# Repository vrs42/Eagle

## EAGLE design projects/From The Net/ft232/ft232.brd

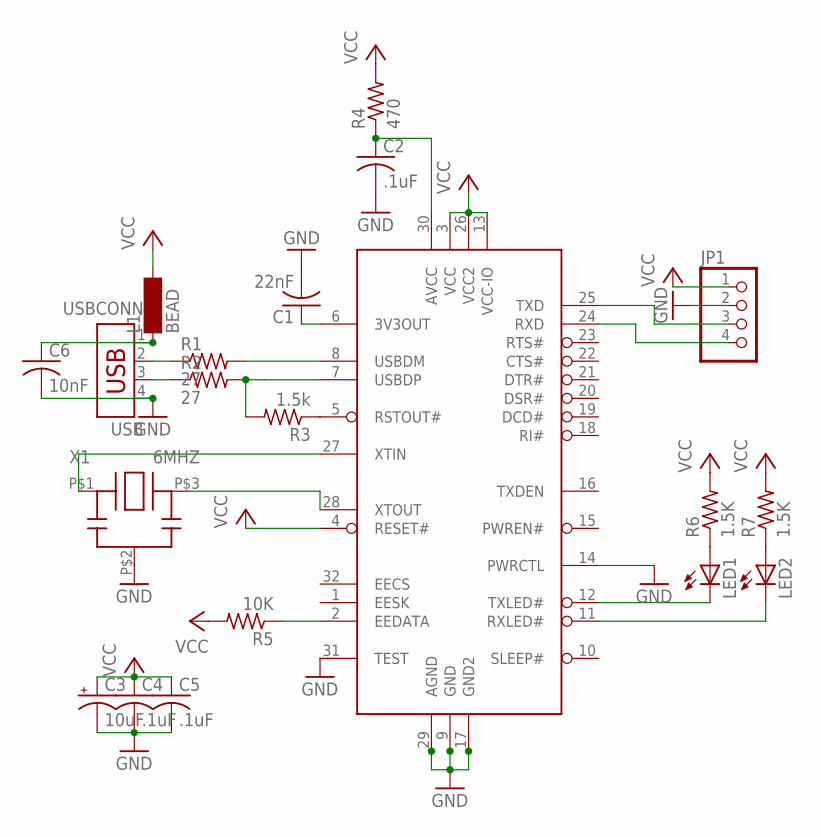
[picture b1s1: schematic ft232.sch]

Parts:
C1: 22nF; C1206
C2, C4, C5: .1uF; C1206
C3: 10uF; B/3528-21R
C6: 10nF; C1206
IC1: FT232; SQFP-S-7X7-32
JP1: PINHD-1X4; 1X04
L1: BEAD; SM-1206
LED1, LED2: LEDSMT1206; 1206
R1, R2: 27; R1206
R3: 1.5k; R1206
R4: 470; R1206
R5: 10K; R1206
R6, R7: 1.5K; R1206
USBCONN: USB
X1: 6MHZ; ZTT_XTAL

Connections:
GND: C1.2, C2.2, C3.-, C4.2, C5.2, C6.2, IC1.9 (GND), IC1.14 (PWRCTL), IC1.17 (GND2), IC1.29 (AGND), IC1.31 (TEST), JP1.2, USBCONN.4, X1.P$2 (GND)
unnamed: R1.1, USBCONN.2
unnamed: R2.1, USBCONN.3
unnamed: IC1.7 (USBDP), R2.2, R3.2
unnamed: IC1.8 (USBDM), R1.2
unnamed: IC1.5 (RSTOUT#), R3.1
unnamed: C2.1, IC1.30 (AVCC), R4.1
unnamed: C1.1, IC1.6 (3V3OUT)
unnamed: IC1.2 (EEDATA), R5.1
unnamed: IC1.28 (XTOUT), X1.P$3 (OUT)
unnamed: IC1.27 (XTIN), X1.P$1 (IN)
unnamed: IC1.25 (TXD), JP1.3
unnamed: IC1.24 (RXD), JP1.4
unnamed: IC1.11 (RXLED#), LED2.C
unnamed: IC1.12 (TXLED#), LED1.C
unnamed: LED1.A, R6.1
unnamed: LED2.A, R7.1
unnamed: C6.1, L1.1, USBCONN.1
VCC: C3.+, C4.1, C5.1, IC1.3 (VCC), IC1.4 (RESET#), IC1.13 (VCC-IO), IC1.26 (VCC2), JP1.1, L1.2, R4.2, R5.2, R6.2, R7.2

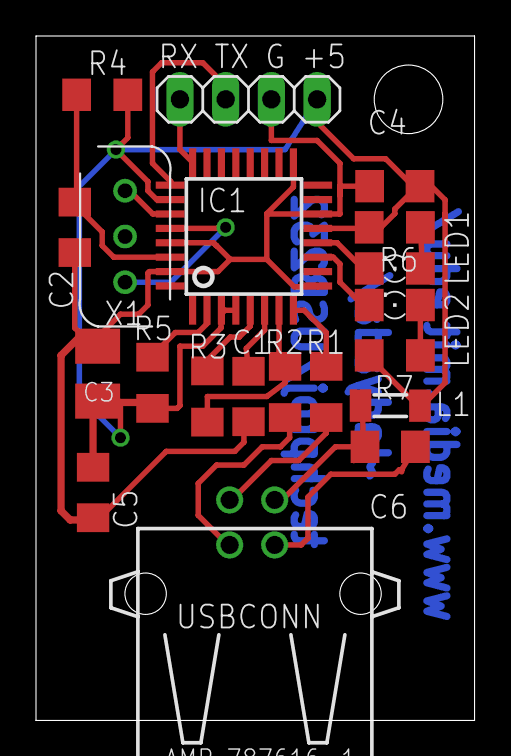
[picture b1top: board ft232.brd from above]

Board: 2 copper layers, 24.4 x 38.0 mm, 20 parts (0 on the bottom side), 19 nets.

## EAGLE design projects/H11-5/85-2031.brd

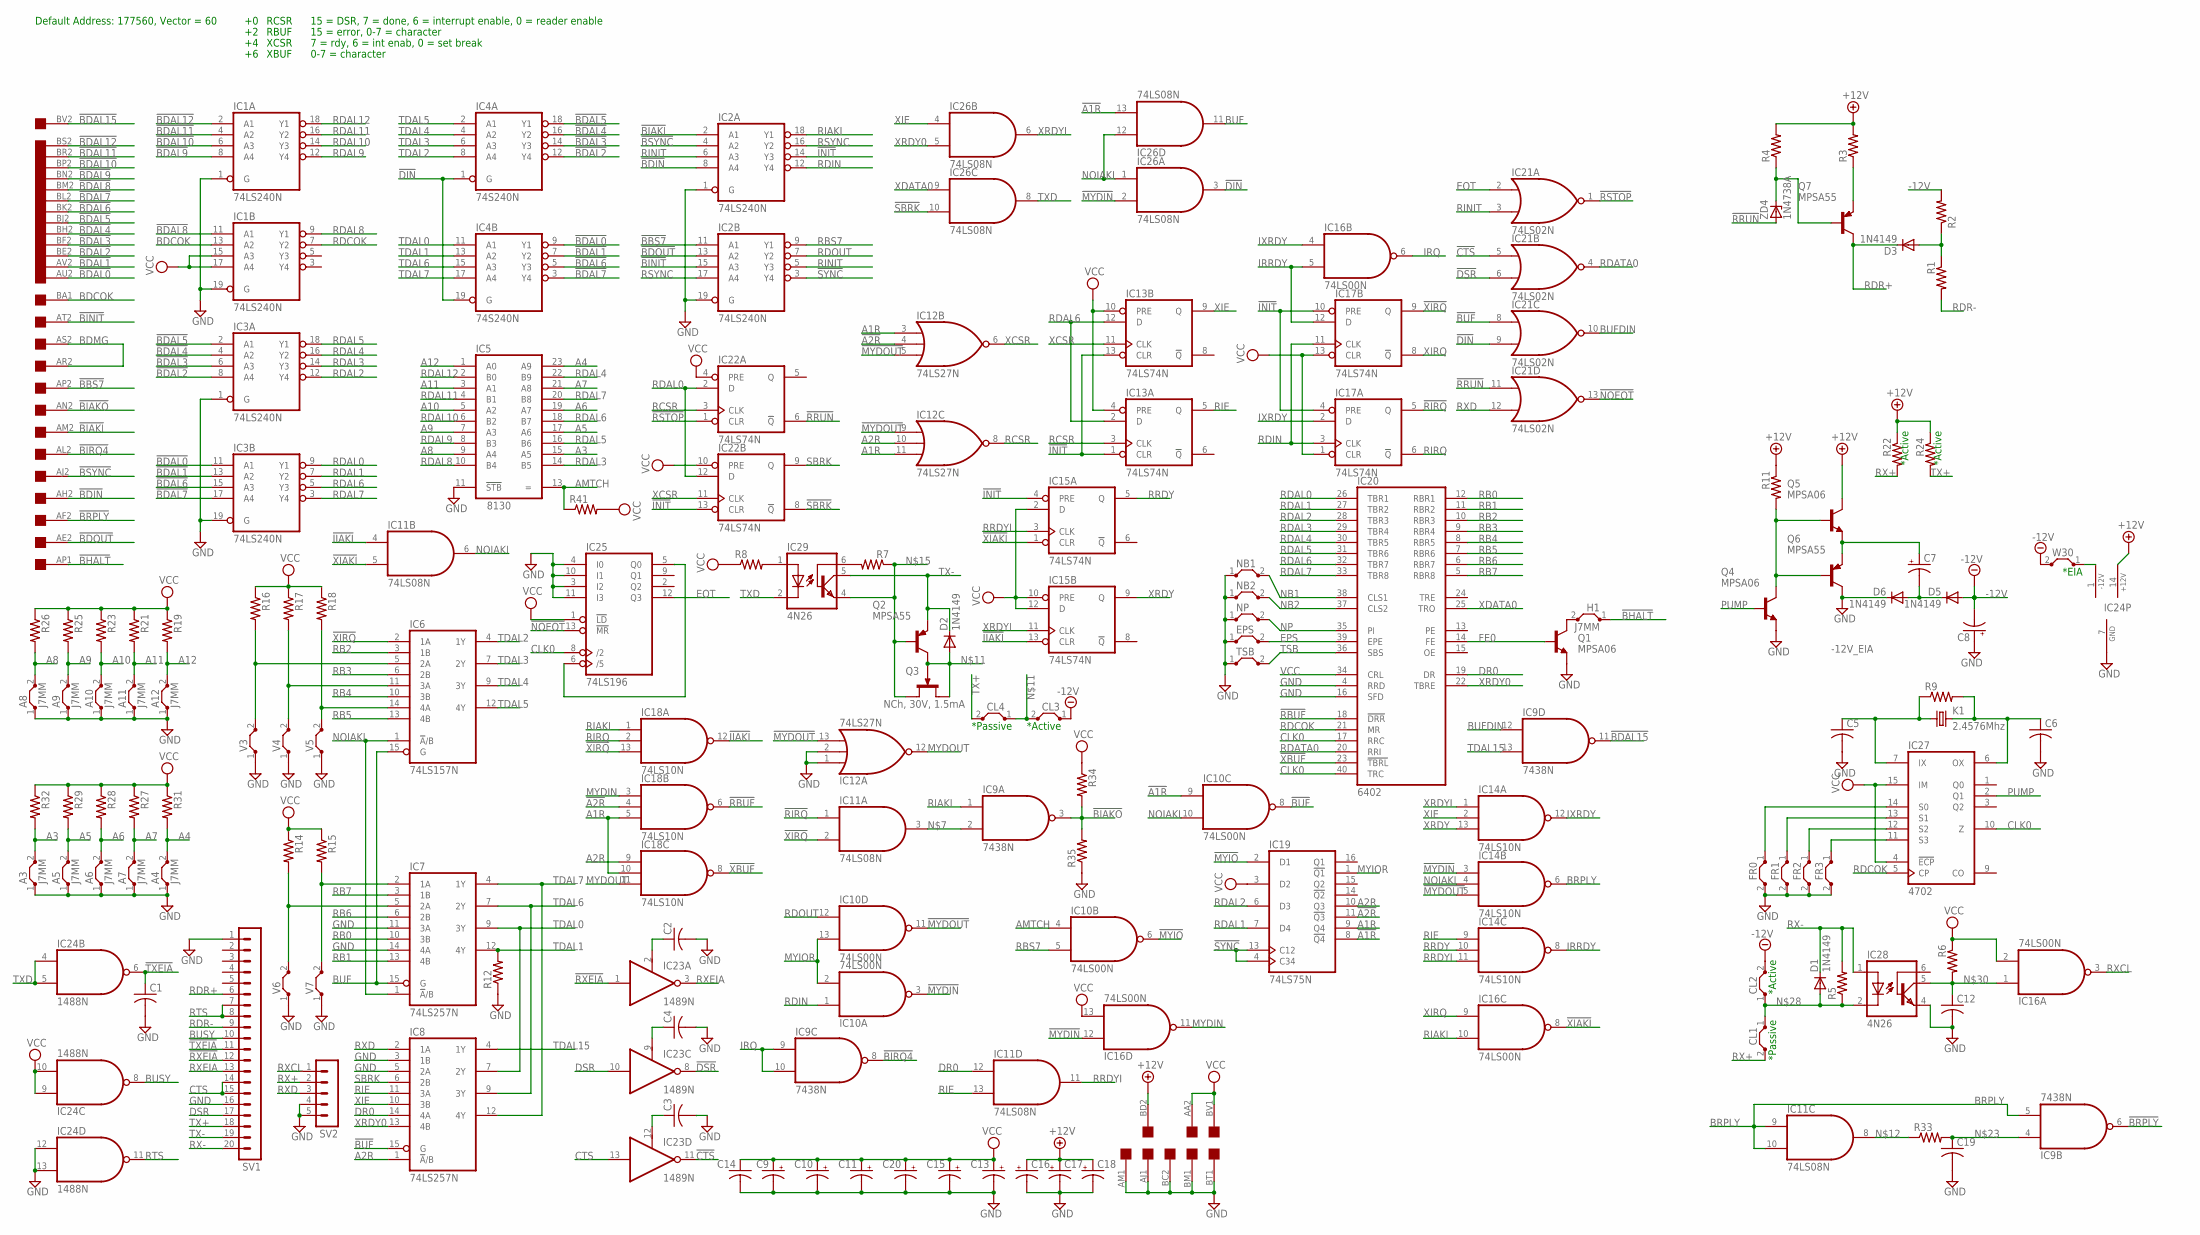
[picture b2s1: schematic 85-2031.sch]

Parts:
A3, A4, A5, A6, A7, A8, A9, A10, A11, A12: J7MM; 07
C1, C2, C3, C4, C5, C6, C12, C14, C19: C-US075-032X103; C075-032X103
C7, C8, C9, C10, C11, C13, C15, C16, C17, C18, C20: CPOL-USB45181B; B45181B
CL1, CL2, CL3, CL4: J7MM; 07
D1, D2, D3, D5, D6: 1N4149; DO35-10
EDGE$: DOUBLE; EDGE-CON4
EPS: J7MM; 07
FR0, FR1, FR2, FR3: J7MM; 07
H1: J7MM; 07
IC1, IC2, IC3: 74LS240N; DIL20
IC4: 74S240N; DIL20
IC5: 8130; DIL24
IC6: 74LS157N; DIL16
IC7, IC8: 74LS257N; DIL16
IC9: 7438N; DIL14
IC10, IC16: 74LS00N; DIL14
IC11, IC26: 74LS08N; DIL14
IC12: 74LS27N; DIL14
IC13, IC15, IC17, IC22: 74LS74N; DIL14
IC14, IC18: 74LS10N; DIL14
IC19: 74LS75N; DIL16
IC20: 6402; DIL40
IC21: 74LS02N; DIL14
IC23: 1489N; DIL14
IC24: 1488N; DIL14
IC25: 74LS196; DIL14
IC27: 4702; DIL16
IC28, IC29: 4N26; DIL06
K1: 2.4576Mhz; HC33U-H
NB1, NB2: J7MM; 07
NP: J7MM; 07
Q1, Q4, Q5: MPSA06; TO92L
Q2, Q6, Q7: MPSA55; TO92L
Q3: NCh, 30V, 1.5mA; TO18E
R1, R2, R3, R4, R5, R6, R7, R8, R9, R12, R14, R15, R16, R17, R18, R19, R21, R22, R23, R24, R25, R26, R27, R28, R29, R31, R32, R33, R34, R35, R41: R-US_0207/10; 0207/10
R11: R-US_0411/12; 0411/12
SV1: MA20-1
SV2: MA05-1
TSB: J7MM; 07
V3, V4, V5, V6, V7: J7MM; 07
W30: J7MM; 07
ZD4: 1N4738A; DO41Z10

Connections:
!A1R: IC10.9 (I0), IC19.8 (!Q4), IC26.13 (I1)
!A2R: IC12.4 (I1), IC18.4 (I1), IC19.11 (!Q3)
!BBS7: EDGE$.AP2, IC2.11 (A1)
!BDAL0: EDGE$.AU2, IC3.11 (A1), IC4.9 (Y1)
!BDAL1: EDGE$.AV2, IC3.13 (A2), IC4.7 (Y2)
!BDAL2: EDGE$.BE2, IC3.8 (A4), IC4.12 (Y4)
!BDAL3: EDGE$.BF2, IC3.6 (A3), IC4.14 (Y3)
!BDAL4: EDGE$.BH2, IC3.4 (A2), IC4.16 (Y2)
!BDAL5: EDGE$.BJ2, IC3.2 (A1), IC4.18 (Y1)
!BDAL6: EDGE$.BK2, IC3.15 (A3), IC4.5 (Y3)
!BDAL7: EDGE$.BL2, IC3.17 (A4), IC4.3 (Y4)
!BDAL8: EDGE$.BM2, IC1.11 (A1)
!BDAL9: EDGE$.BN2, IC1.8 (A4)
!BDAL10: EDGE$.BP2, IC1.6 (A3)
!BDAL11: EDGE$.BR2, IC1.4 (A2)
!BDAL12: EDGE$.BS2, IC1.2 (A1)
!BDAL15: EDGE$.BV2, IC9.11 (O)
!BDIN: EDGE$.AH2, IC2.8 (A4)
!BDOUT: EDGE$.AE2, IC2.13 (A2)
!BHALT: EDGE$.AP1, H1.1
!BIAKI: EDGE$.AM2, IC2.2 (A1)
!BIAKO: EDGE$.AN2, IC9.3 (O), R34.2, R35.2
!BINIT: EDGE$.AT2, IC2.15 (A3)
!BIRQ4: EDGE$.AL2, IC9.8 (O)
!BRPLY: EDGE$.AF2, IC9.6 (O)
!BSYNC: EDGE$.AJ2, IC2.4 (A2)
!BUF: IC8.15 (G), IC10.8 (O), IC21.8 (I0)
!CTS: IC21.5 (I0), IC23.11 (O)
!DIN: IC4.1 (G), IC4.19 (G), IC21.9 (I1), IC26.3 (O)
!DSR: IC21.6 (I1), IC23.8 (O)
!IIAKI: IC11.4 (I0), IC15.13 (CLR), IC18.12 (O)
!INIT: IC2.14 (Y3), IC13.1 (CLR), IC13.13 (CLR), IC15.4 (PRE), IC17.4 (PRE), IC17.10 (PRE), IC22.13 (CLR)
!MYDIN: IC10.3 (O), IC14.3 (I0), IC16.12 (I0), IC26.2 (I1)
!MYDOUT: IC10.11 (O), IC12.5 (I2), IC12.9 (I0), IC12.13 (I2), IC14.5 (I2)
!MYIO: IC10.6 (O), IC19.2 (D1)
!NOEOT: IC21.13 (O), IC25.13 (!MR)
!RBUF: IC18.6 (O), IC20.18 (!DRR)
!RIRQ: IC11.1 (I0), IC17.5 (Q)
!RRUN: IC21.11 (I0), IC22.6 (!Q), ZD4.A
!RSTOP: IC21.1 (O), IC22.1 (CLR)
!RXEIA: IC23.1 (I), SV1.12
!SBRK: IC22.8 (!Q), IC26.10 (I1)
!SYNC: IC2.3 (Y4), IC19.4 (C34), IC19.13 (C12)
!TXEIA: C1.1, IC24.6 (O), SV1.11
!XBUF: IC18.8 (O), IC20.23 (!TBRL)
!XIAKI: IC11.5 (I1), IC15.1 (CLR), IC16.8 (O)
!XIRQ: IC6.2 (1A), IC11.2 (I1), IC17.9 (Q), IC18.13 (I2)
+12V: C16.+, C17.+, C18.+, EDGE$.BD2, IC24.14 (+12V), Q5.3 (C), R3.2, R4.2, R11.1, R22.1, R24.1
-12V: C8.-, CL2.2, CL3.1, D5.A, R2.2, W30.2
-12V_EIA: IC24.1 (-12V), W30.1
A1R: IC12.3 (I0), IC12.11 (I2), IC18.5 (I2), IC18.10 (I1), IC19.9 (Q4)
A2R: IC8.1 (!A!/B), IC12.10 (I1), IC18.9 (I0), IC19.10 (Q3)
A3: A3.2, IC5.15 (A5), R32.2
A4: A4.2, IC5.23 (A9), R31.2
A5: A5.2, IC5.17 (A6), R29.2
A6: A6.2, IC5.19 (A7), R28.2
A7: A7.2, IC5.21 (A8), R27.2
A8: A8.2, IC5.9 (A4), R26.2
A9: A9.2, IC5.7 (A3), R25.2
A10: A10.2, IC5.5 (A2), R23.2
A11: A11.2, IC5.3 (A1), R21.2
A12: A12.2, IC5.1 (A0), R19.2
AMTCH: IC5.13 (=), IC10.4 (I0), R41.1
BDCOK: EDGE$.BA1, IC1.13 (A2)
BDMG: EDGE$.AR2, EDGE$.AS2
BRPLY: IC9.5 (I1), IC11.9 (I0), IC11.10 (I1), IC14.6 (O)
BUF: IC6.15 (G), IC7.15 (G), IC26.11 (O)
BUFDIN: IC9.12 (I0), IC21.10 (O)
BUSY: IC24.8 (O), SV1.10
CLK0: IC20.17 (RRC), IC20.40 (TRC), IC25.8 (/2), IC27.10 (Z)
CTS: IC23.13 (I), SV1.14, SV1.15
DR0: IC8.14 (4A), IC11.12 (I0), IC20.19 (DR)
DSR: IC23.10 (I), SV1.17
EOT: IC21.2 (I0), IC25.12 (Q3)
EPS: EPS.2, IC20.39 (EPE)
FE0: IC20.14 (FE), Q1.2 (B)
GND: A3.1, A4.1, A5.1, A6.1, A7.1, A8.1, A9.1, A10.1, A11.1, A12.1, C1.2, C2.2, C3.2, C4.2, C5.2, C6.2, C8.+, C9.-, C10.-, C11.-, C12.2, C13.-, C14.2, C15.-, C16.-, C17.-, C18.-, C19.2, C20.-, D6.C, EDGE$.AJ1, EDGE$.AM1, EDGE$.BC2, EDGE$.BM1, EDGE$.BT1, EPS.1, FR0.2, FR1.2, FR2.2, FR3.2, IC1.1 (G), IC1.10 (GND), IC1.19 (G), IC2.1 (G), IC2.10 (GND), IC2.19 (G), IC3.1 (G), IC3.10 (GND), IC3.19 (G), IC4.10 (GND), IC5.11 (!STB), IC5.12 (GND), IC6.8 (GND), IC7.8 (GND), IC7.11 (3A), IC7.14 (4A), IC8.3 (1B), IC8.5 (2A), IC8.8 (GND), IC9.7 (GND), IC10.7 (GND), IC11.7 (GND), IC12.1 (I0), IC12.2 (I1), IC12.7 (GND), IC13.7 (GND), IC14.7 (GND), IC15.7 (GND), IC16.7 (GND), IC17.7 (GND), IC18.7 (GND), IC19.12 (GND), IC20.3 (GND), IC20.4 (RRD), IC20.16 (SFD), IC21.7 (GND), IC22.7 (GND), IC23.7 (GND), IC24.7 (GND), IC24.12 (I0), IC24.13 (I1), IC25.3 (I2), IC25.4 (I0), IC25.7 (GND), IC25.10 (I1), IC25.11 (I3), IC26.7 (GND), IC27.8 (GND), IC28.4 (EMI), NB1.1, NB2.1, NP.1, Q1.1 (E), Q4.1 (E), Q6.3 (C), R12.1, R35.1, SV1.1, SV1.16, SV2.4, SV2.5, TSB.1, V3.1, V4.1, V5.1, V6.1, V7.1
IRQ: IC9.9 (I0), IC9.10 (I1), IC16.6 (O)
IRRDY: IC14.8 (O), IC16.5 (I1), IC17.12 (D)
IXRDY: IC14.12 (O), IC16.4 (I0), IC17.2 (D)
MYDIN: IC16.11 (O), IC18.3 (I0)
MYDOUT: IC12.12 (O), IC18.11 (I2)
MYIOR: IC10.2 (I1), IC10.13 (I1), IC19.1 (!Q1)
unnamed: C2.1, IC23.2 (RC)
unnamed: FR0.1, IC27.14 (S0)
unnamed: H1.2, Q1.3 (C)
unnamed: FR1.1, IC27.13 (S1)
unnamed: FR2.1, IC27.12 (S2)
unnamed: FR3.1, IC27.11 (S3)
unnamed: IC9.2 (I1), IC11.3 (O)
unnamed: IC6.14 (4A), R18.2, V5.2
unnamed: C5.1, IC27.7 (IX), K1.1, R9.1
unnamed: C6.1, IC27.6 (OX), K1.2, R9.2
unnamed: CL3.2, CL4.1, D2.A, Q2.3 (C), Q3.D, Q3.G
unnamed: IC11.8 (O), R33.1
unnamed: IC29.6 (BAS), R7.2
unnamed: IC29.4 (EMI), Q2.2 (B), Q3.S, R7.1
unnamed: IC29.1 (A), R8.2
unnamed: IC7.2 (1A), R15.2, V7.2
unnamed: IC7.5 (2A), R14.2, V6.2
unnamed: C4.1, IC23.9 (RC)
unnamed: C7.-, D5.C, D6.A
unnamed: IC6.11 (3A), R17.2, V4.2
unnamed: C7.+, Q5.1 (E), Q6.1 (E)
unnamed: C19.1, IC9.4 (I0), R33.2
unnamed: IC6.5 (2A), R16.2, V3.2
unnamed: C3.1, IC23.12 (RC)
unnamed: Q4.3 (C), Q5.2 (B), Q6.2 (B), R11.2
unnamed: D3.A, R1.1, R2.1
unnamed: CL1.1, CL2.1, D1.A, IC28.2 (C), R5.1
unnamed: Q7.2 (B), R4.1, ZD4.C
unnamed: C12.1, IC16.1 (I0), IC28.5 (COL), R6.2
unnamed: Q7.1 (E), R3.1
unnamed: IC25.5 (Q0), IC25.6 (/5)
NB1: IC20.38 (CLS1), NB1.2
NB2: IC20.37 (CLS2), NB2.2
NOIAKI: IC6.1 (!A!/B), IC7.1 (!A!/B), IC10.10 (I1), IC11.6 (O), IC14.4 (I1), IC26.1 (I0), IC26.12 (I0)
NP: IC20.35 (PI), NP.2
PUMP: IC27.2 (Q1), Q4.2 (B)
RB0: IC7.10 (3B), IC20.12 (RBR1)
RB1: IC7.13 (4B), IC20.11 (RBR2)
RB2: IC6.3 (1B), IC20.10 (RBR3)
RB3: IC6.6 (2B), IC20.9 (RBR4)
RB4: IC6.10 (3B), IC20.8 (RBR5)
RB5: IC6.13 (4B), IC20.7 (RBR6)
RB6: IC7.6 (2B), IC20.6 (RBR7)
RB7: IC7.3 (1B), IC20.5 (RBR8)
RBS7: IC2.9 (Y1), IC10.5 (I1)
RCSR: IC12.8 (O), IC13.3 (CLK), IC22.3 (CLK)
RDAL0: IC3.9 (Y1), IC20.26 (TBR1), IC22.2 (D), IC22.12 (D)
RDAL1: IC3.7 (Y2), IC19.7 (D4), IC20.27 (TBR2)
RDAL2: IC3.12 (Y4), IC19.6 (D3), IC20.28 (TBR3)
RDAL3: IC3.14 (Y3), IC5.14 (B5), IC20.29 (TBR4)
RDAL4: IC3.16 (Y2), IC5.22 (B9), IC20.30 (TBR5)
RDAL5: IC3.18 (Y1), IC5.16 (B6), IC20.31 (TBR6)
RDAL6: IC3.5 (Y3), IC5.18 (B7), IC13.2 (D), IC13.12 (D), IC20.32 (TBR7)
RDAL7: IC3.3 (Y4), IC5.20 (B8), IC20.33 (TBR8)
RDAL8: IC1.9 (Y1), IC5.10 (B4)
RDAL9: IC1.12 (Y4), IC5.8 (B3)
RDAL10: IC1.14 (Y3), IC5.6 (B2)
RDAL11: IC1.16 (Y2), IC5.4 (B1)
RDAL12: IC1.18 (Y1), IC5.2 (B0)
RDATA0: IC20.20 (RRI), IC21.4 (O)
RDCOK: IC1.7 (Y2), IC20.21 (MR), IC27.5 (CP)
RDIN: IC2.12 (Y4), IC10.1 (I0), IC17.3 (CLK), IC17.11 (CLK)
RDOUT: IC2.7 (Y2), IC10.12 (I0)
RDR+: D3.C, Q7.3 (C), SV1.6
RDR-: R1.2, SV1.9
RIAKI: IC2.18 (Y1), IC9.1 (I0), IC16.10 (I1), IC18.1 (I0)
RIE: IC8.11 (3A), IC11.13 (I1), IC13.5 (Q), IC14.9 (I0)
RINIT: IC2.5 (Y3), IC2.6 (A3), IC21.3 (I1)
RIRQ: IC17.6 (!Q), IC18.2 (I1)
RRDY: IC14.10 (I1), IC15.5 (Q)
RRDYI: IC11.11 (O), IC14.11 (I2), IC15.3 (CLK)
RSYNC: IC2.16 (Y2), IC2.17 (A4)
RTS: IC24.11 (O), SV1.7, SV1.8
RX+: CL1.2, R22.2, SV2.2
RX-: D1.C, IC28.1 (A), R5.2, SV1.20
RXCL: IC16.3 (O), SV2.1
RXD: IC8.2 (1A), IC21.12 (I1), SV2.3
RXEIA: IC23.3 (O), SV1.13
SBRK: IC8.6 (2B), IC22.9 (Q)
TDAL0: IC4.11 (A1), IC7.9 (3Y), IC8.7 (2Y)
TDAL1: IC4.13 (A2), IC7.12 (4Y), R12.2
TDAL2: IC4.8 (A4), IC6.4 (1Y)
TDAL3: IC4.6 (A3), IC6.7 (2Y)
TDAL4: IC4.4 (A2), IC6.9 (3Y)
TDAL5: IC4.2 (A1), IC6.12 (4Y)
TDAL6: IC4.15 (A3), IC7.7 (2Y), IC8.9 (3Y)
TDAL7: IC4.17 (A4), IC7.4 (1Y), IC8.12 (4Y)
TDAL15: IC8.4 (1Y), IC9.13 (I1)
TSB: IC20.36 (SBS), TSB.2
TX+: CL4.2, R24.2, SV1.18
TX-: D2.C, IC29.5 (COL), Q2.1 (E), SV1.19
TXD: IC24.4 (I0), IC24.5 (I1), IC26.8 (O), IC29.2 (C)
VCC: C9.+, C10.+, C11.+, C13.+, C14.1, C15.+, C20.+, EDGE$.AA2, EDGE$.BV1, IC1.15 (A3), IC1.17 (A4), IC1.20 (VCC), IC2.20 (VCC), IC3.20 (VCC), IC4.20 (VCC), IC5.24 (VCC), IC6.16 (VCC), IC7.16 (VCC), IC8.16 (VCC), IC9.14 (VCC), IC10.14 (VCC), IC11.14 (VCC), IC12.14 (VCC), IC13.4 (PRE), IC13.10 (PRE), IC13.14 (VCC), IC14.14 (VCC), IC15.2 (D), IC15.10 (PRE), IC15.12 (D), IC15.14 (VCC), IC16.2 (I1), IC16.13 (I1), IC16.14 (VCC), IC17.1 (CLR), IC17.13 (CLR), IC17.14 (VCC), IC18.14 (VCC), IC19.3 (D2), IC19.5 (VCC), IC20.1 (VCC), IC20.34 (CRL), IC21.14 (VCC), IC22.4 (PRE), IC22.10 (PRE), IC22.14 (VCC), IC23.14 (VCC), IC24.9 (I0), IC24.10 (I1), IC25.1 (!LD), IC25.14 (VCC), IC26.14 (VCC), IC27.4 (!ECP), IC27.15 (IM), IC27.16 (VCC), R6.1, R8.1, R14.1, R15.1, R16.1, R17.1, R18.1, R19.1, R21.1, R23.1, R25.1, R26.1, R27.1, R28.1, R29.1, R31.1, R32.1, R34.1, R41.2
XCSR: IC12.6 (O), IC13.11 (CLK), IC22.11 (CLK)
XDATA0: IC20.25 (TRO), IC26.9 (I0)
XIE: IC8.10 (3B), IC13.9 (Q), IC14.2 (I1), IC26.4 (I0)
XIRQ: IC16.9 (I0), IC17.8 (!Q)
XRDY: IC14.13 (I2), IC15.9 (Q)
XRDY0: IC8.13 (4B), IC20.22 (TBRE), IC26.5 (I1)
XRDYI: IC14.1 (I0), IC15.11 (CLK), IC26.6 (O)

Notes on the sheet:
RCSR
RBUF
XCSR
XBUF
15 = DSR, 7 = done, 6 = interrupt enable, 0 = reader enable
15 = error, 0-7 = character
7 = rdy, 6 = int enab, 0 = set break
0-7 = character
Default Address: 177560, Vector = 60
*Passive
*Active
*EIA

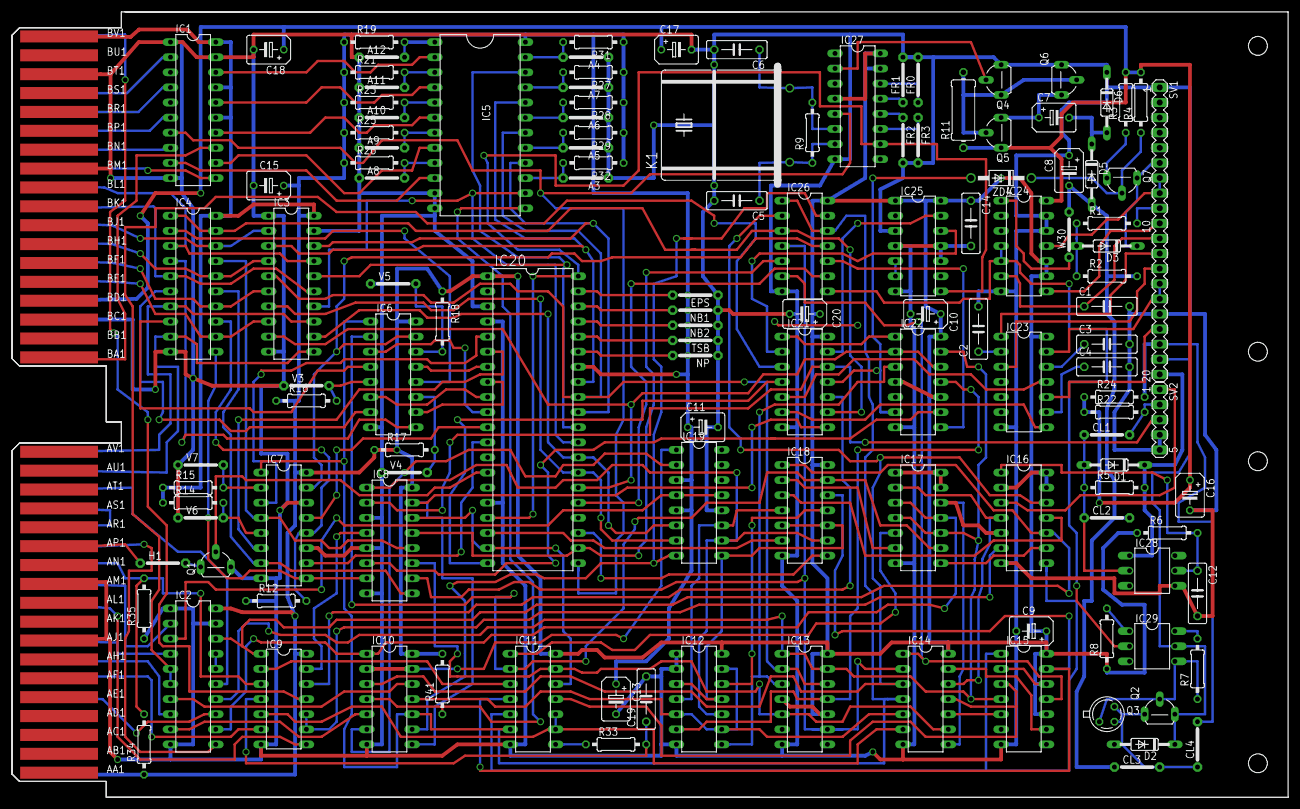
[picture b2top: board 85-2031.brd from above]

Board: 2 copper layers, 214.6 x 132.1 mm, 129 parts (0 on the bottom side), 183 nets.

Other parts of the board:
E$2: DOUBLE-LONG
